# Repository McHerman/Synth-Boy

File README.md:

# Synth-Boy
## Probably the worlds smallest analog USB powered parafonic synthesizer. 

## Techical details 

The Synthboy is an analog 3 oscilator FM-enabled parafonic synthesizer, with a 4 pole voltage controlled filter, an analog ADSR envelope generator and onboard beyboard and TRS Midi control. 
The whole thing is powered from a single protected USB-C input.

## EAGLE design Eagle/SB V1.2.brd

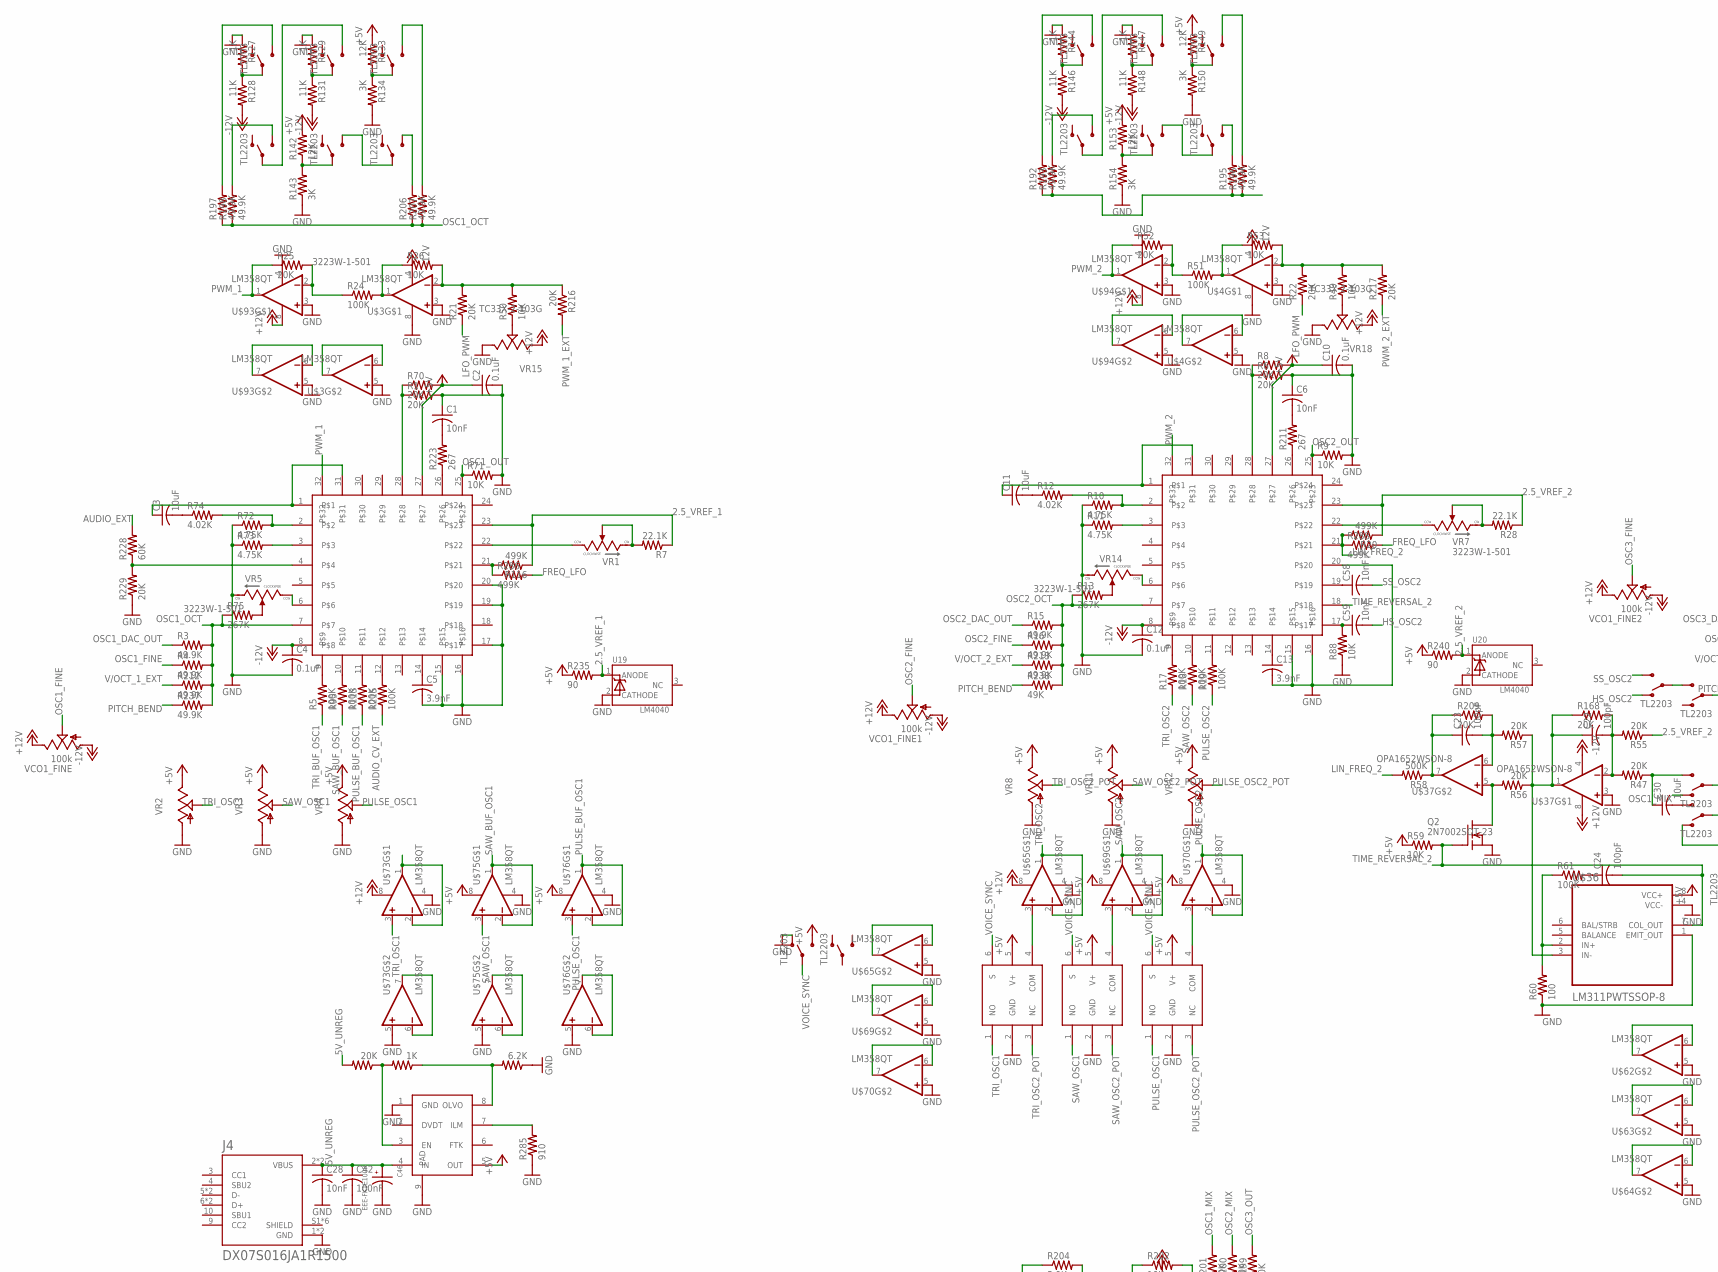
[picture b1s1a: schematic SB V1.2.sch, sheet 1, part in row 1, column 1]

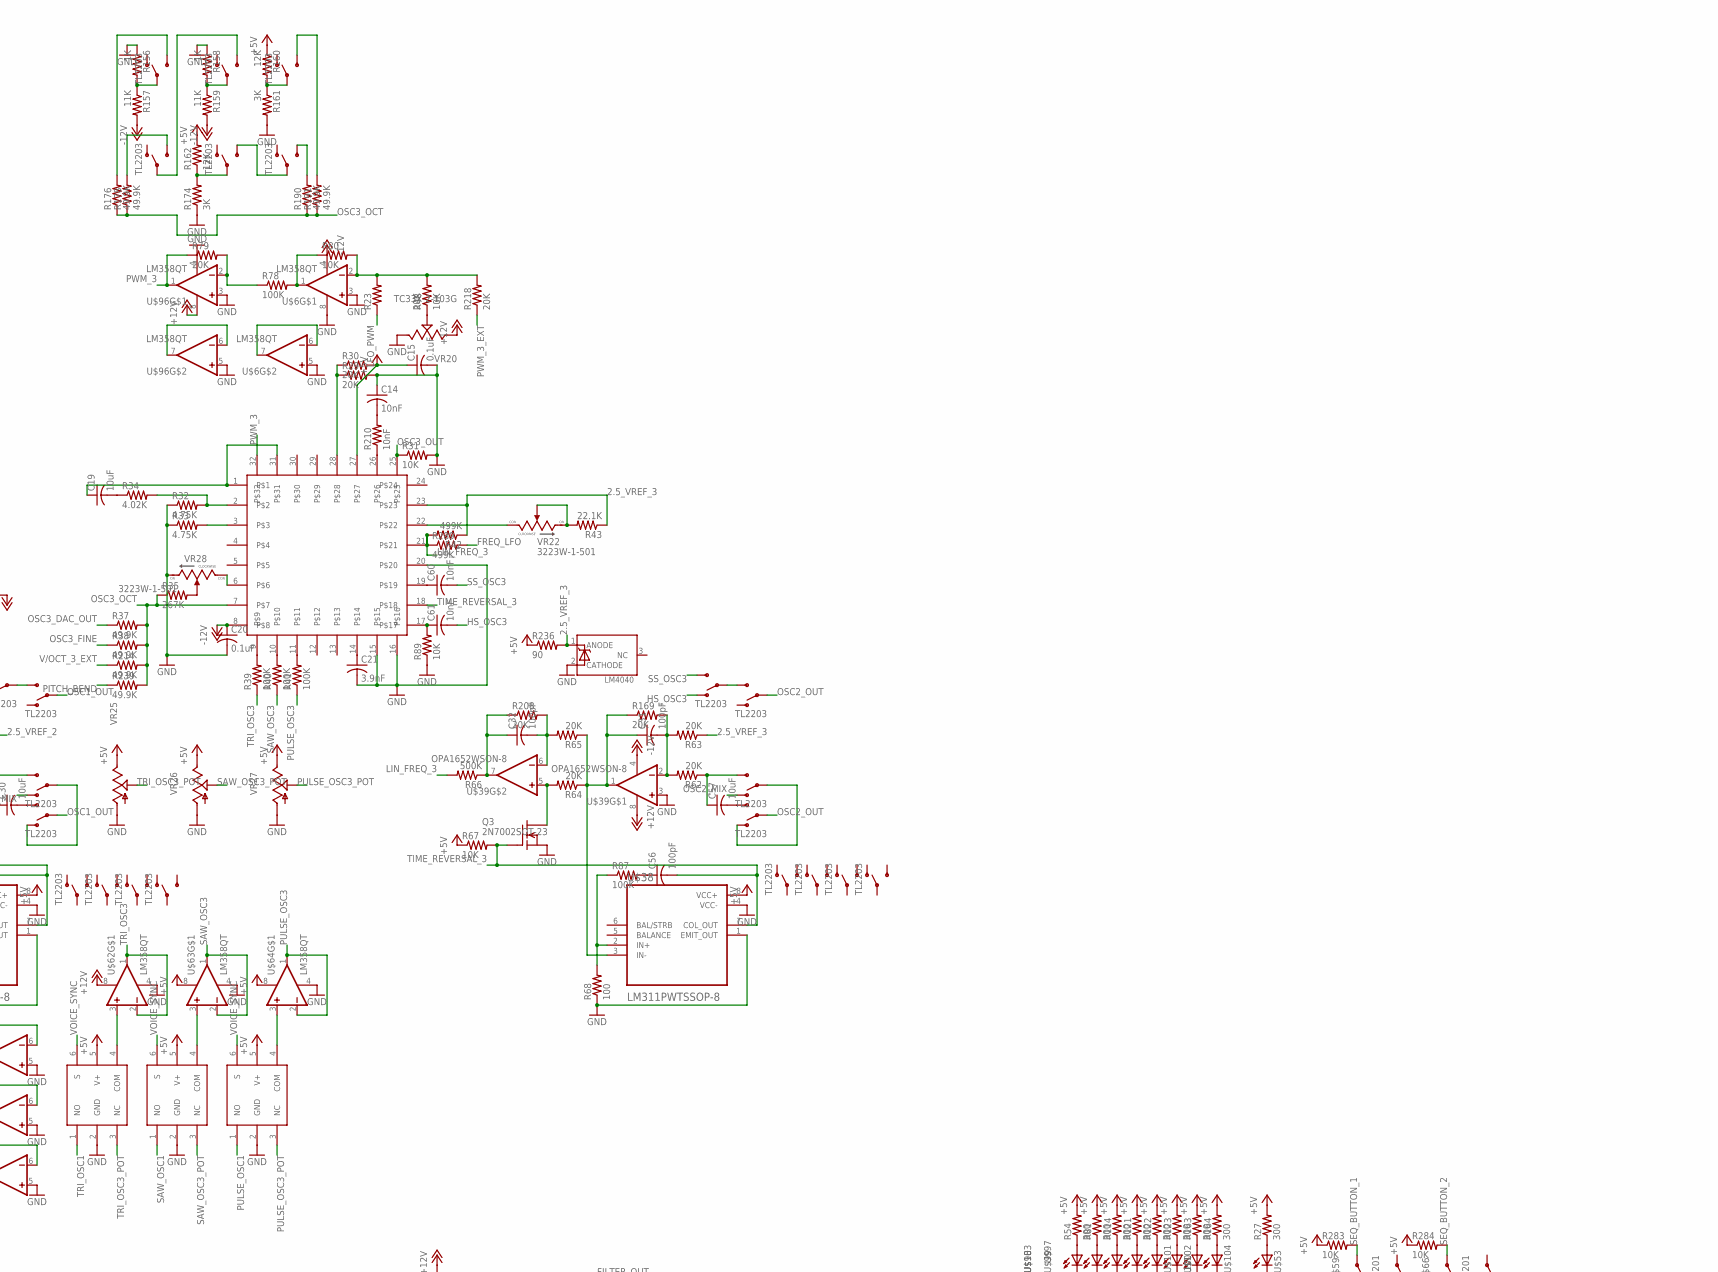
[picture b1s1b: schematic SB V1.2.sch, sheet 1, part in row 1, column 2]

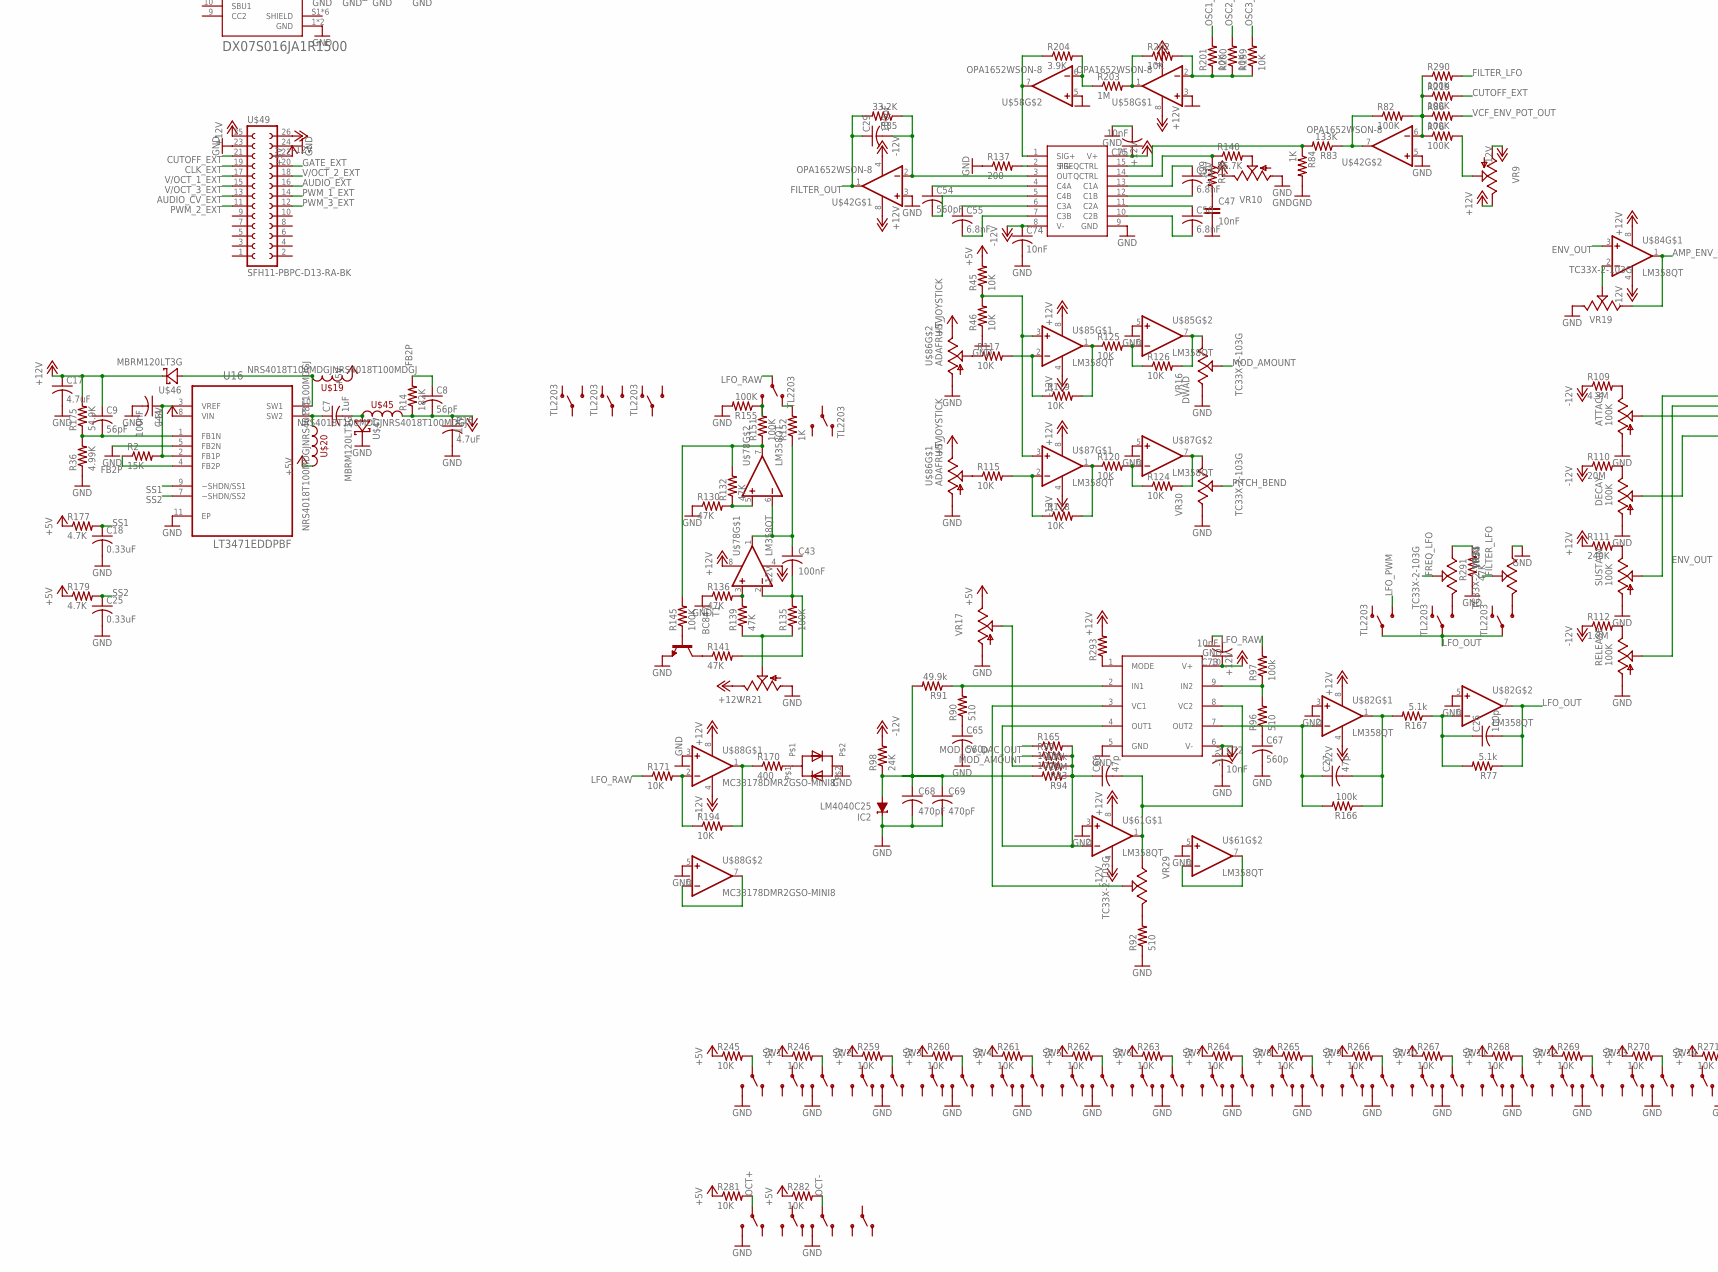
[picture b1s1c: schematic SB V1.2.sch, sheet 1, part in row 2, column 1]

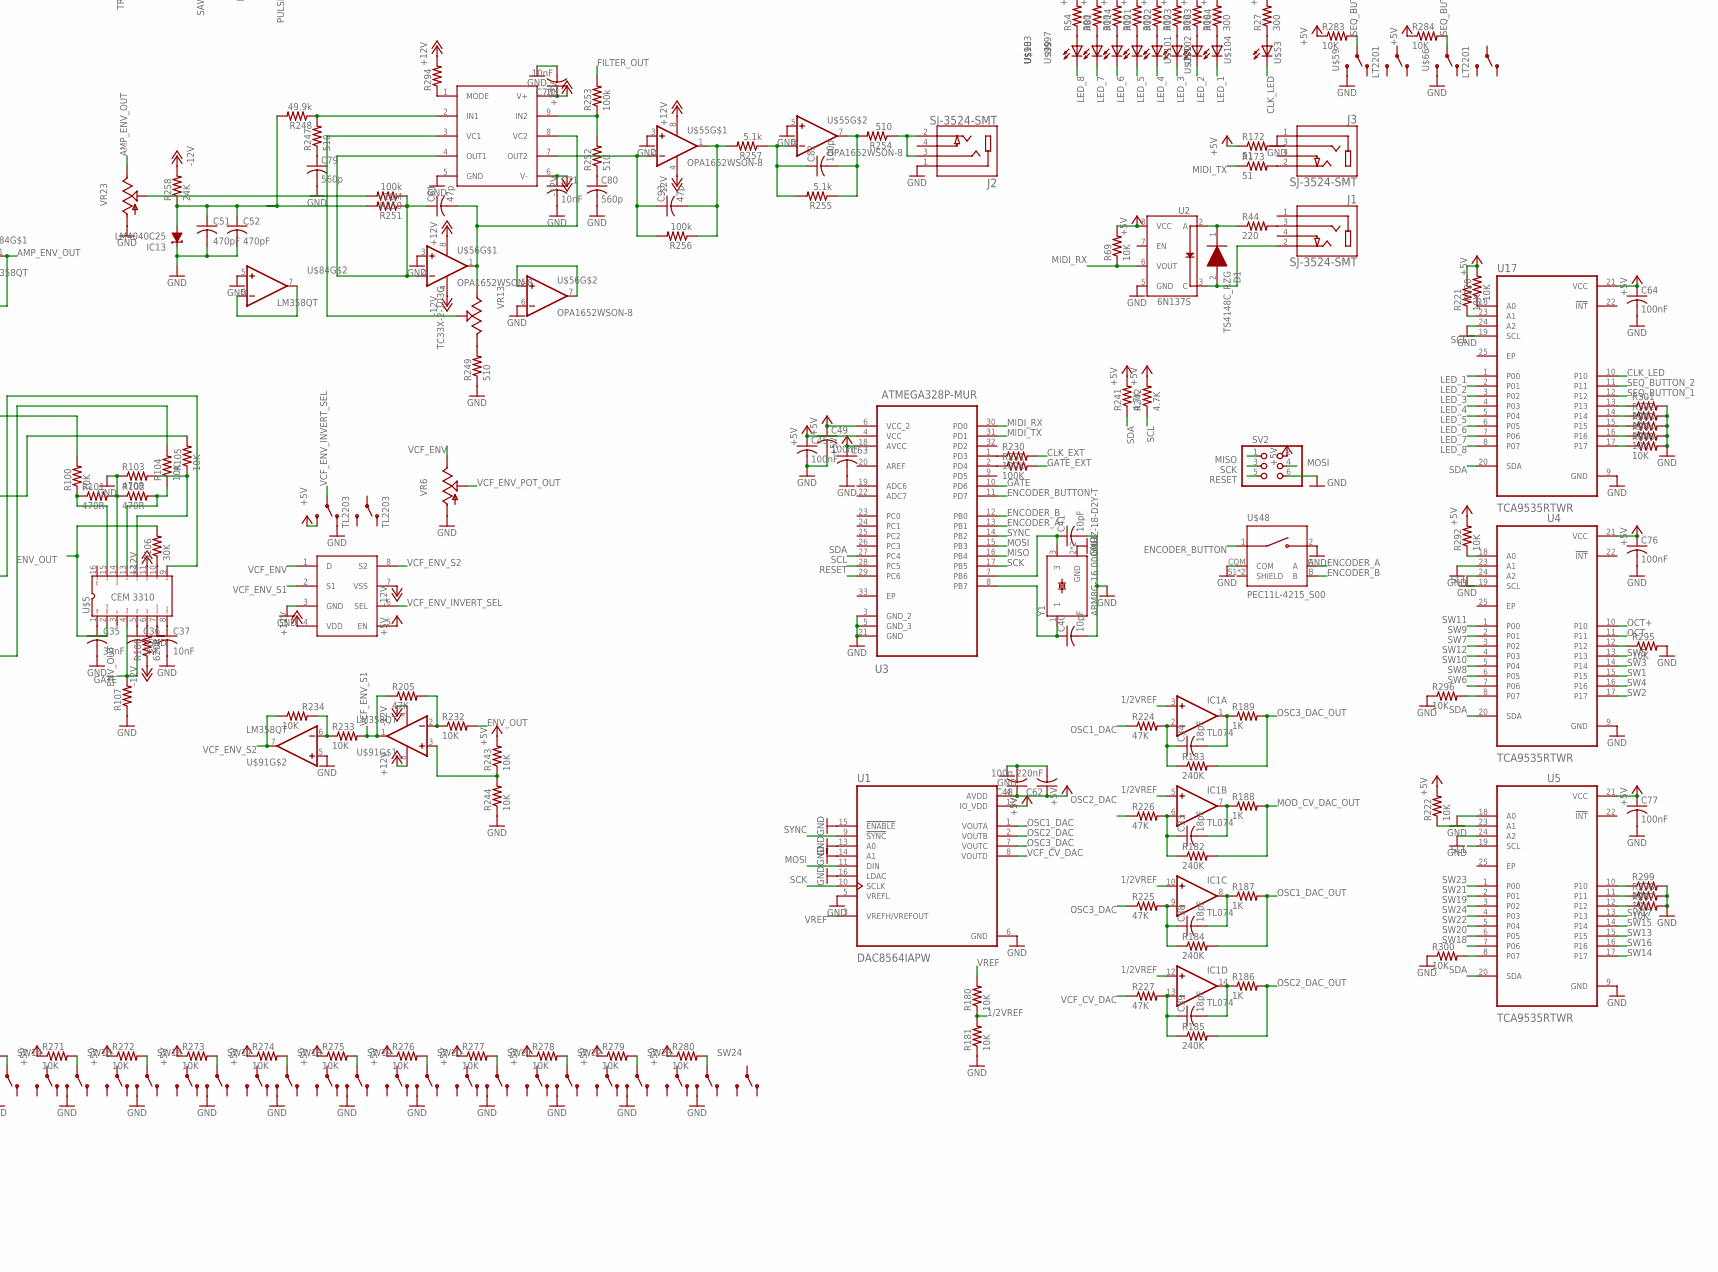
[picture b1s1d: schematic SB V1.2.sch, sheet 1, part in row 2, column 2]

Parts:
1.2K: 1K; R0402
1_DOWN, 1_UP, 2_DOWN, 2_UP, 3_DOWN, 3_UP: TL2203
4.3K: 20K; R0402
ATTACK: 100K; 9MM_SNAP-IN_POT
C1, C6, C14, C37, C47, C58, C59, C60, C61, C70, C71, C72, C73, C74, C75: 10nF; C0402
C2, C4, C10, C12, C15, C20: 0.1uF; C0402
C3, C11, C19, C30, C57: 10uF; C0603
C5, C13, C21: 3.9nF; C0603
C7: 1uF; C0805
C8, C9: 56pF; C0402
C16, C17: 4.7uF; C1206
C18, C25: 0.33uF; C0402
C22, C23, C24, C29, C31, C32, C56: 100pF; C0402
C26, C82: 100p; C0402
C27, C66, C81, C93: 47p; C0402
C28: 10nF; C0603
C33, C34, C38, C39: 18pF; C0402
C35: 39nF; C0402
C36: 3nF; C0402
C40, C41: 10pF; C0402
C42: 100nF; C0603
C43, C44, C45, C49, C64, C76, C77: 100nF; C0402
C46: EEE-FK1E100R; CAPAE430X610N
C48: 100n; C0402
C50, C53, C55: 6.8nF; C0805
C51, C52, C68, C69: 470pF; C0402
C54: 560pF; C0805
C62: 220nF; C0402
C63: C-USC0402; C0402
C65, C67, C79, C80: 560p; C0402
D1: TS4148C_RZG; DIOC1608X75N
DECAY: 100K; 9MM_SNAP-IN_POT
IC1: TL074; TSSOP14
IC2, IC13: LM4040C25; DBZ_R-PDSO-G3
J1, J2, J3: SJ-3524-SMT; CUI_SJ-3524-SMT
J4: DX07S016JA1R1500; JAE_DX07S016JA1R1500
Q2, Q3: 2N7002SOT-23; SOT23-BEC
R1, R6, R8, R21, R22, R23, R25, R29, R30, R47, R52, R55, R56, R57, R62, R63, R64, R65, R70, R79, R168, R169, R208, R209, R216, R217, R218, R229: 20K; R0402
R2: 15K; R0402
R3, R4, R15, R16, R37, R38, R176, R178, R190, R191, R192, R193, R195, R196, R197, R198, R206, R207, R212, R213, R214, R237, R239: 49.9K; R0402
R5, R17, R18, R19, R24, R39, R40, R41, R51, R61, R76, R78, R82, R86, R87, R95, R99, R113, R135, R145, R151, R155, R165, R215, R219, R230, R231, R290: 100K; R0402
R7, R28, R43: 22.1K; R0402
R9, R26, R31, R45, R46, R48, R49, R50, R53, R59, R67, R69, R71, R80, R88, R89, R100, R104, R105, R107, R115, R117, R118, R119, R120, R124, R125, R126, R171, R180, R181, R194, R199, R200, R201, R202, R220, R221, R222, R232, R233, R234, R243, R244, R245, R246, R259, R260, R261, R262, R263, R264, R265, R266, R267, R268, R269, R270, R271, R272, R273, R274, R275, R276, R277, R278, R279, R280, R281, R282, R283, R284, R292, R295, R296, R297, R298, R299, R300, R301, R302, R303, R304, R305: 10K; R0402
R10, R11, R32, R33, R72, R73: 4.75K; R0402
R12, R34, R74: 4.02K; R0402
R13, R35, R75: 267K; R0402
R14: 182K; R0402
R20, R42, R116, R286, R288, R289: 499K; R0402
R27, R54, R81, R114, R121, R122, R123, R163, R164: 300; R0603
R36: 4.99K; R0402
R44: 220; R0402
R58, R66: 500K; R0402
R60, R68: 100; R0402
R77, R167, R255, R257: 5.1k; R0402
R83: 133K; R0402
R84, R127, R129, R144, R147, R152, R156, R158, R186, R187, R188, R189: 1K; R0402
R85: 33.2K; R0402
R90, R92, R96, R247, R249, R252, R254: 510; R0402
R91, R248: 49.9k; R0402
R93, R97, R166, R250, R253, R256: 100k; R0402
R94, R110, R251: 20M; R0402
R98, R258: 24K; R0402
R101, R102, R103: 470R; R0402
R106: 30K; R0402
R108: 620R; R0402
R109: 4.3M; R0402
R111, R182, R183, R184, R185: 240K; R0402
R112: 1.8M; R0402
R128, R131, R146, R148, R157, R159: 11K; R0402
R130, R132, R136, R139, R141, R205, R224, R225, R226, R227, R291: 47K; R0402
R133, R142, R149, R153, R160, R162: 12K; R0402
R134, R143, R150, R154, R161, R174: 3K; R0402
R137: 200; R0402
R138: 499; R0402
R140: 26.7K; R0402
R170: 400; R0603
R172, R173: 51; R0402
R175: 54.9K; R0402
R177, R179, R241, R242: 4.7K; R0402
R203: 1M; R0402
R204: 3.9K; R0402
R210: 10nF; R0402
R211, R223: 267; R0402
R228: 60K; R0402
R235, R236, R240: 90; R0402
R238: 49K; R0402
R285: 910; R0402
R287: 6.2K; R0402
R293, R294: R-US_R0402; R0402
RELEASE: 100K; 9MM_SNAP-IN_POT
SUSTAIN: 100K; 9MM_SNAP-IN_POT
SV2: PINHD-2X3; 2X03
T1: BC847; SOT23
U1: DAC8564IAPW; SOP65P640X120-16N
U2: 6N137S; 8-SMD
U3: ATMEGA328P-MUR; QFN50P500X500X100-33N
U4, U5, U17: TCA9535RTWR; QFN50P400X400X80-25N
U16: LT3471EDDPBF; DFN300X300X80-11N
U19, U20, U21: LM4040; SOT23-3
U$1, U$2, U$7: SSI2130_V2QFN-32; QFN40P400X400X80-33T270N
U$3, U$4, U$6, U$61, U$62, U$63, U$64, U$65, U$69, U$70, U$73, U$75, U$76, U$78, U$82, U$84, U$85, U$87, U$91, U$93, U$94, U$96: LM358QT; SON50P200X200X60-9N
U$5: AS3310DSO-16; SO16
U$8, U$35, U$40, U$41, U$43, U$44, U$51, U$57, U$60, U$71, U$72, U$77, U$79, U$80, U$81, U$92, U$95: TL2203
U$9, U$10, U$11, U$12, U$13, U$14, U$15, U$16, U$17, U$18, U$21, U$22, U$23, U$24, U$25, U$26, U$27, U$28, U$29, U$30, U$31, U$32, U$33, U$34, U$59, U$66, U$67, U$68: LT2201
U$19, U$20, U$45: NRS4018T100MDGJNRS4018T100MDGJ; INDDFN400X400X180-2N
U$36, U$38: LM311PWTSSOP-8; TSSOP8
U$37, U$39, U$42, U$55, U$56, U$58: OPA1652WSON-8; SON50P300X300X80-9T120X200N
U$46, U$47: MBRM120LT3G; DIO_MBRM110LT1G
U$48: PEC11L-4215_S00; XDCR_PEC11R-4215F-S0024
U$49: SFH11-PBPC-D13-RA-BK; FE13-2W
U$53, U$97, U$98, U$99, U$100, U$101, U$102, U$103, U$104: WP914HDT
U$54, U$90: SSI2162SSOP10; SOP100P600X150-10N
U$74: WP483SRSGW
U$83: SSI2144; TSSOP16
U$86: ADAFRUIT_JOYSTICK; ADAFRUIT-JOYSTICK
U$88: MC33178DMR2GSO-MINI8; SOP65P490X110-8N
U$89: TMUX6219DGKRSO-MINI8; SOP65P490X110-8N
U$105, U$106, U$107, U$108, U$109, U$110: NC7SB3157P6XSC-70-6; SOT65P210X110-6N
U$111: TPS259620DDARSOIC-8; SOIC127P600X170-9T240X310N
VCO1_FINE, VCO1_FINE1, VCO1_FINE2: 100k; 9MM_SNAP-IN_POT
VR1, VR5, VR7, VR14, VR22, VR28: 3223W-1-501; TRIM_3223W-1-501
VR2, VR3, VR4, VR6, VR8, VR9, VR10, VR11, VR12, VR17, VR23, VR25, VR26, VR27: 9MM_SNAP-IN_POT_; 9MM_SNAP-IN_POT
VR13, VR15, VR16, VR18, VR19, VR20, VR24, VR29, VR30, VR31: TC33X-2-103G; TRIMMER_TC33X-2-103G
VR21: 9MM_SNAP-IN_POT_NOSNAP_; 9MM_SNAP-IN_POT
Y1: ABM8G-16.000MHZ-18-D2Y-T; OSCSC320X250X100N

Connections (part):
1/2VREF: IC1.3 (+IN), IC1.5 (+IN), IC1.10 (+IN), IC1.12 (+IN), R180.1, R181.2
2.5_VREF_1: R7.1, R116.1, R235.2, U19.1 (ANODE), U$7.23
2.5_VREF_2: R20.1, R28.1, R55.1, R240.2, U20.1 (ANODE), U$1.23
2.5_VREF_3: R42.1, R43.1, R63.1, R236.2, U21.1 (ANODE), U$2.23
5V_UNREG: 4.3K.2, C28.1, C42.1, C46.1, J4.2 (VBUS), J4.11 (VBUS), U$111.4 (IN)
+5V: C2.1, C10.1, C15.1, C45.1, C48.1, C49.1, C62.1, C63.1, C64.1, C76.1, C77.1, R8.2, R27.2, R30.2, R45.2, R54.2, R59.1, R67.1, R69.2, R70.2, R81.2, R114.2, R121.2, R122.2, R123.2, R133.1, R142.2, R149.1, R153.2, R160.1, R162.2, R163.2, R164.2, R172.1, R177.1, R179.1, R220.2, R221.2, R222.2, R235.1, R236.1, R240.1, R241.2, R242.2, R243.2, R245.1, R246.1, R259.1, R260.1, R261.1, R262.1, R263.1, R264.1, R265.1, R266.1, R267.1, R268.1, R269.1, R270.1, R271.1, R272.1, R273.1, R274.1, R275.1, R276.1, R277.1, R278.1, R279.1, R280.1, R281.1, R282.1, R283.1, R284.1, R292.2, SV2.2, U1.4 (AVDD), U1.12 (IO_VDD), U2.8 (VCC), U3.4 (VCC), U3.6 (VCC_2)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
+12V: C9.1, C17.1, C70.1, C73.1, C75.1, IC1.4 (V+), R111.1, R175.2, R293.2, R294.2, U$5.11, U$37.8 (V+), U$39.8 (V+), U$42.8 (V+), U$46.1 (K), U$49.25, U$54.10 (V+), U$55.8 (V+), U$56.8 (V+), U$58.8 (V+), U$61.8 (V+), U$62.8 (V+), U$65.8 (V+), U$73.8 (V+), U$78.8 (V+), U$82.8 (V+), U$83.16 (V+), U$84.8 (V+), U$85.8 (V+), U$87.8 (V+), U$88.8 (V+), U$89.4 (VDD), U$90.10 (V+), U$91.8 (V+), U$93.8 (V+), U$94.8 (V+), U$96.8 (V+), VCO1_FINE.3 (E), VCO1_FINE1.3 (E), VCO1_FINE2.3 (E), VR9.3 (E), VR10.3 (E), VR15.1 (CCW), VR18.1 (CCW), VR20.1 (CCW), VR21.3 (E)
-12V: C4.1, C8.2, C12.1, C16.1, C20.1, C71.1, C72.1, C74.1, IC1.11 (V-), R14.1, R98.2, R108.1, R109.1, R110.1, R112.1, R128.2, R131.2, R146.2, R148.2, R157.2, R159.2, R258.2, U$1.8, U$2.8, U$3.4 (V-), U$4.4 (V-), U$6.4 (V-), U$7.8, U$37.4 (V-), U$39.4 (V-), U$42.4 (V-), U$45.2, U$49.26, U$54.6 (V-), U$55.4 (V-), U$56.4 (V-), U$58.4 (V-), U$61.4 (V-), U$78.4 (V-), U$82.4 (V-), U$83.8 (V-), U$84.4 (V-), U$85.4 (V-), U$87.4 (V-), U$88.4 (V-), U$89.7 (VSS), U$90.6 (V-), U$91.4 (V-), VCO1_FINE.1 (A), VCO1_FINE1.1 (A), VCO1_FINE2.1 (A), VR9.1 (A)
AMP_ENV_OUT: U$84.1 (OUT), VR19.1 (CCW), VR23.3 (E)
AREF_-2.1: C51.1, C52.1, IC13.2 (A), R248.2, R251.2, R258.1
AREF_-2.2: C68.1, C69.1, IC2.2 (A), R91.2, R94.2, R98.1
AUDIO_CV_EXT: R215.1, U$49.13
AUDIO_EXT: R228.2, U$49.16
A_IN_O2B1: R247.2, R248.1, U$54.2 (IN1)
A_IN_O2B2: R90.2, R91.1, U$90.2 (IN1)
CLK_EXT: R230.2, U$49.19
CLK_LED: U17.10, U$53.C
CUTOFF_EXT: R219.2, U$49.21
DWAD: R126.2, U$85.7 (OUT), VR16.3 (CW)
ENCODER_A: U3.13 (PB1), U$48.A
ENCODER_B: U3.12 (PB0), U$48.B
ENCODER_BUTTON: U3.11 (PD7), U$48.1
ENV_OUT: R106.2, R232.2, U$5.2, U$84.3 (+IN)
FB2P: C8.1, R2.1, R14.2, U16.4 (FB2P)
FILTER_LFO: R290.2, VR31.2 (WIPER)
FILTER_OUT: C29.1, R85.2, R253.2, U$42.1 (OUT)
FREQ_LFO: R286.2, R288.2, R289.2, VR24.2 (WIPER)
GATE: C36.2, R107.2, U3.10 (PD6), U$5.4
GATE_EXT: R231.2, U$49.20
GND: ATTACK.1 (A), C1.1, C2.2, C4.2, C5.2, C6.1, C10.2, C12.2, C13.2, C14.1, C15.2, C16.2, C17.2, C18.2, C20.2, C21.2, C25.2, C28.2, C35.2, C37.2, C40.2, C41.2, C42.2, C44.2, C45.2, C46.2, C47.2, C48.2, C49.2, C51.2, C52.2, C62.2, C63.2, C64.2, C65.2, C67.2, C68.2, C69.2, C70.2, C71.2, C72.2, C73.2, C74.2, C75.2, C76.2, C77.2, C79.2, C80.2, DECAY.1 (A), IC2.1 (C), IC13.1 (C), J2.1, J3.1, J4.1 (GND), J4.12 (GND), Q2.C (S), Q3.C (S), R1.2, R6.2, R9.2, R10.1, R11.1, R29.2, R31.2, R32.1, R33.1, R36.1, R46.1, R60.1, R68.1, R71.2, R72.1, R73.1, R84.2, R88.1, R89.1, R92.1, R101.2, R102.1, R103.1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
HS_OSC2: C59.2, U$51.P$3 (O1)
HS_OSC3: C61.2, U$57.P$3 (O1)
LED_1: U17.1 (P00), U$104.C
LED_2: U17.2 (P01), U$103.C
LED_3: U17.3 (P02), U$102.C
LED_4: U17.4 (P03), U$101.C
LED_5: U17.5 (P04), U$100.C
LED_6: U17.6 (P05), U$99.C
LED_7: U17.7 (P06), U$98.C
LED_8: U17.8 (P07), U$97.C
LFO_OUT: C26.2, R77.1, U$79.P$2 (COMMON1), U$80.P$2 (COMMON1), U$81.P$2 (COMMON1), U$82.7 (OUT)
LFO_PWM: R21.1, R22.1, R23.1, U$79.P$1 (S1)
LFO_RAW: R97.2, R171.1, U$77.P$2 (COMMON1)
LIN_FREQ_2: R20.2, R58.2, R288.1, U$1.21
LIN_FREQ_3: R42.2, R66.2, R289.1, U$2.21
MIDI_RX: R69.1, U2.6 (VOUT), U3.30 (PD0)
MIDI_TX: R173.1, U3.31 (PD1)
MISO: SV2.1, U3.16 (PB4)
MIX2_OUT: R204.1, U$58.7 (OUT), U$83.1 (SIG+)
MOD_AMOUNT: R99.1, VR16.2 (WIPER)
MOD_CV_DAC_OUT: R165.1, R182.2, R188.2
MOSI: SV2.4, U1.11 (DIN), U3.15 (PB3)
unnamed: R5.2, U$7.9
unnamed: C30.2, U$8.P$1 (S1)
unnamed: C57.2, U$40.P$1 (S1)
unnamed: R116.2, R286.1, U$7.21
unnamed: U$7.22, VR1.1
unnamed: R7.2, VR1.2, VR1.3
unnamed: U$84.2 (-IN), VR19.2 (WIPER)
unnamed: R6.1, R8.1, U$1.28
unnamed: U$8.P$3 (O1), U$35.P$2 (COMMON1)
unnamed: U$7.6, VR5.1
unnamed: R210.1, U$2.26
unnamed: R27.1, U$53.A
unnamed: R75.2, VR5.2
unnamed: U$40.P$3 (O1), U$41.P$2 (COMMON1)
unnamed: R10.2, R12.2, U$1.2
unnamed: C11.2, R12.1
unnamed: C11.1, U$1.1, U$1.31
unnamed: R132.2, R145.2, R151.1, U$78.7 (OUT)
unnamed: R17.2, U$1.9
unnamed: R18.2, U$1.10
unnamed: R19.2, U$1.11
unnamed: C13.1, U$1.14
unnamed: R54.1, U$97.A
unnamed: U$93.6 (-IN), U$93.7 (OUT)
unnamed: U$1.22, VR7.1
unnamed: R29.1, R30.1, U$2.28
unnamed: R24.2, R26.1, U$3.1 (OUT)
unnamed: R28.2, VR7.2, VR7.3
unnamed: U$65.3 (+IN), U$105.4 (COM)
unnamed: R24.1, R25.2, U$93.2 (-IN)
unnamed: R199.1, R200.1, R201.1, R202.2, U$58.2 (-IN)
unnamed: R170.2, U$74.P$1
unnamed: R11.2, U$1.3
unnamed: U$43.P$1 (S1), U$51.P$2 (COMMON1)
unnamed: C44.1, R2.2, U16.2 (FB1P), U16.3 (VREF)
unnamed: U$1.6, VR14.1
unnamed: R13.2, VR14.2
unnamed: U$44.P$1 (S1), U$57.P$2 (COMMON1)
unnamed: U$69.3 (+IN), U$106.4 (COM)
unnamed: C22.2, R47.2, R55.2, R168.2, U$37.2 (-IN)
unnamed: C14.2, R210.2
unnamed: R32.2, R34.2, U$2.2
unnamed: C19.2, R34.1
unnamed: C19.1, U$2.1, U$2.31
unnamed: C9.2, R36.2, R175.1, U16.1 (FB1N)
unnamed: R39.2, U$2.9
unnamed: R40.2, U$2.10
unnamed: R41.2, U$2.11
unnamed: C21.1, U$2.14
unnamed: U$70.3 (+IN), U$107.4 (COM)
unnamed: U$2.22, VR22.1
unnamed: R43.2, VR22.2, VR22.3
unnamed: R33.2, U$2.3
unnamed: C22.1, R56.1, R57.1, R168.1, U$36.3 (IN-), U$37.1 (OUT)
unnamed: U$2.6, VR28.1
unnamed: R35.2, VR28.2
unnamed: C32.2, R65.2, R208.2, U$39.6 (-IN)
unnamed: C23.1, R58.1, R209.1, U$37.7 (OUT)
unnamed: Q3.E (D), R64.2, U$39.5 (+IN)
unnamed: R51.2, R53.1, U$4.1 (OUT)
unnamed: R51.1, R52.2, U$94.2 (-IN)
unnamed: C43.1, R152.1, U$78.1 (OUT), U$78.6 (-IN)
unnamed: R171.2, R194.1, U$88.2 (-IN)
unnamed: R60.2, R61.1, U$36.2 (IN+)
unnamed: C24.1, R61.2
unnamed: U$62.3 (+IN), U$108.4 (COM)
unnamed: C30.1, R47.1, U$35.P$1 (S1)
unnamed: R115.1, U$86.P$2 (S)
unnamed: C31.2, R62.2, R63.2, R169.2, U$39.2 (-IN)
unnamed: C31.1, R64.1, R65.1, R169.1, U$38.3 (IN-), U$39.1 (OUT)
unnamed: Q2.E (D), R56.2, U$37.5 (+IN)
unnamed: C32.1, R66.1, R208.1, U$39.7 (OUT)
unnamed: C23.2, R57.2, R209.2, U$37.6 (-IN)
unnamed: R68.2, R87.1, U$38.2 (IN+)
unnamed: C56.1, R87.2
unnamed: C57.1, R62.1, U$41.P$1 (S1)
unnamed: R1.1, R70.1, U$7.28
unnamed: R211.1, U$1.26
unnamed: R72.2, R74.2, U$7.2
unnamed: C3.2, R74.1
unnamed: C3.1, U$7.1, U$7.31
unnamed: C7.1, U16.6 (SW2), U$20.1
unnamed: R78.2, R80.1, U$6.1 (OUT)
unnamed: R78.1, R79.2, U$96.2 (-IN)
unnamed: R136.2, R139.2, U$78.3 (+IN)
unnamed: D1.1 (K), R44.1, U2.2 (A)
unnamed: D1.2 (A), J1.2, U2.3 (C)
unnamed: R170.1, R194.2, U$88.1 (OUT)
unnamed: J1.3, R44.2
unnamed: U$88.6 (-IN), U$88.7 (OUT)
unnamed: C6.2, R211.2
unnamed: R95.2, U$7.10
unnamed: R113.2, U$7.11
unnamed: C58.1, U$1.19
unnamed: R233.1, R234.2, U$91.6 (-IN)
unnamed: C59.1, R88.2, U$1.17
unnamed: R76.1, R82.2, R86.1, R219.1, R290.1, U$42.6 (-IN)
unnamed: R221.1, U17.23 (A1)
unnamed: C66.1, R93.1, R94.1, R99.2, R165.2, U$61.2 (-IN), U$90.4 (OUT1)
unnamed: C61.1, R89.2, U$2.17
unnamed: C93.1, R256.2, U$54.7 (OUT2), U$55.2 (-IN)
unnamed: R76.2, VR9.2 (S)
unnamed: C60.1, U$2.19
unnamed: U$63.3 (+IN), U$109.4 (COM)
unnamed: U$64.3 (+IN), U$110.4 (COM)
unnamed: U$62.6 (-IN), U$62.7 (OUT)
unnamed: U$63.6 (-IN), U$63.7 (OUT)
unnamed: U$64.6 (-IN), U$64.7 (OUT)
unnamed: U$65.6 (-IN), U$65.7 (OUT)
unnamed: U$69.6 (-IN), U$69.7 (OUT)
unnamed: U$70.6 (-IN), U$70.7 (OUT)
unnamed: R117.1, U$86.P$5 (S)
unnamed: C5.1, U$7.14
unnamed: R81.1, U$98.A
unnamed: R117.2, R119.1, U$85.2 (-IN)
unnamed: U$73.6 (-IN), U$73.7 (OUT)
unnamed: U$75.6 (-IN), U$75.7 (OUT)
unnamed: U$76.6 (-IN), U$76.7 (OUT)
unnamed: C65.1, R90.1
unnamed: R92.2, VR29.3 (CW)
unnamed: U$90.3 (VC1), VR29.2 (WIPER)
unnamed: C66.2, U$61.1 (OUT), U$90.8 (VC2), VR29.1 (CCW)
unnamed: C67.1, R96.1
unnamed: C27.1, R166.2, U$82.2 (-IN), U$90.7 (OUT2)
unnamed: C55.1, U$83.6 (C3A)
unnamed: R96.2, R97.1, U$90.9 (IN2)
unnamed: R119.2, R125.1, U$85.1 (OUT)
unnamed: R100.1, R101.1, U$5.15
unnamed: R106.1, U$5.10
unnamed: R102.2, R104.1, U$5.13
unnamed: R103.2, R105.1, U$5.12
unnamed: R82.1, R83.1, U$42.7 (OUT)
unnamed: J3.3, R172.2
unnamed: C35.1, U$5.1
unnamed: C36.1, U$5.5
unnamed: C37.1, U$5.8
unnamed: C7.2, U$45.1, U$47.2 (A)
unnamed: J3.2, R173.2
unnamed: R108.2, U$5.6
unnamed: ATTACK.3 (E), R109.2
unnamed: DECAY.3 (E), R110.2
unnamed: R111.2, SUSTAIN.3 (E)
unnamed: R112.2, RELEASE.3 (E)
unnamed: ATTACK.2 (S), R100.2
unnamed: DECAY.2 (S), R105.2
unnamed: SUSTAIN.2 (S), U$5.9
unnamed: R104.2, RELEASE.2 (S)
unnamed: R205.2, R232.1, U$91.2 (-IN)
unnamed: R115.2, R118.1, U$87.2 (-IN)
unnamed: U$84.6 (-IN), U$84.7 (OUT)
unnamed: R223.1, U$7.26
unnamed: U$80.P$1 (S1), VR24.3 (CW)
unnamed: C1.2, R223.2
unnamed: C34.1, IC1.2 (-IN), R183.1, R224.2
unnamed: R73.2, U$7.3
unnamed: R93.2, VR17.2 (S)
unnamed: R118.2, R120.1, U$87.1 (OUT)
unnamed: R120.2, R124.1, U$87.6 (-IN)
unnamed: R114.1, U$99.A
unnamed: R124.2, U$87.7 (OUT), VR30.3 (CW)
unnamed: R125.2, R126.1, U$85.6 (-IN)
unnamed: C39.1, IC1.13 (-IN), R185.1, R227.2
unnamed: C43.2, R135.2, R141.2, U$78.2 (-IN)
unnamed: R250.2, VR23.2 (S)
unnamed: 1_DOWN.P$2 (COMMON1), R127.2, R128.1
unnamed: C38.1, IC1.9 (-IN), R184.1, R225.2
unnamed: C41.1, U3.7 (PB6), Y1.3
unnamed: C33.1, IC1.6 (-IN), R182.1, R226.2
unnamed: C40.1, U3.8 (PB7), Y1.1
unnamed: R129.2, R131.1, U$92.P$2 (COMMON1)
unnamed: U16.10 (SW1), U$19.2, U$46.2 (A)
unnamed: C79.1, R247.1
unnamed: 1_UP.P$5 (COMMON1), R133.2, R134.1
unnamed: R142.1, R143.2, U$92.P$5 (COMMON1)
unnamed: R135.1, R139.1, VR21.2 (S)
unnamed: 1_UP.P$2 (COMMON1), U$92.P$4 (S1)
unnamed: 1_DOWN.P$5 (COMMON1), U$92.P$1 (S1)
unnamed: R202.1, R203.2, U$58.1 (OUT)
unnamed: R141.1, T1.3 (C)
unnamed: C55.2, U$83.7 (C3B)
unnamed: R145.1, T1.1 (B)
unnamed: C53.1, U$83.13 (C1A)
unnamed: 1_DOWN.P$1 (S1), R197.2
unnamed: 1_DOWN.P$4 (S1), R198.2
unnamed: R121.1, U$100.A
unnamed: R122.1, U$101.A
unnamed: R130.2, R132.1, U$78.5 (+IN)
unnamed: C53.2, U$83.12 (C1B)
unnamed: R151.2, R155.1, U$77.P$1 (S1)
unnamed: C50.1, U$83.11 (C2A)
unnamed: R152.2, U$77.P$3 (O1)
unnamed: C50.2, U$83.10 (C2B)
unnamed: 1_UP.P$1 (S1), R206.2
unnamed: 1_UP.P$4 (S1), R207.2
unnamed: 2_DOWN.P$2 (COMMON1), R144.2, R146.1
unnamed: R147.2, R148.1, U$60.P$2 (COMMON1)
unnamed: R123.1, U$102.A
unnamed: 2_UP.P$5 (COMMON1), R149.2, R150.1
unnamed: R163.1, U$103.A
unnamed: R153.1, R154.2, U$60.P$5 (COMMON1)
unnamed: R164.1, U$104.A
unnamed: 2_UP.P$2 (COMMON1), U$60.P$4 (S1)
unnamed: R45.1, R46.2, U$85.3 (+IN), U$87.3 (+IN)
unnamed: C34.2, IC1.1 (OUT), R189.1
unnamed: C33.2, IC1.7 (OUT), R188.1
unnamed: C38.2, IC1.8 (OUT), R187.1
unnamed: C39.2, IC1.14 (OUT), R186.1
unnamed: R297.1, U5.12
unnamed: R298.1, U5.11
unnamed: R299.1, U5.10
unnamed: R300.2, U5.8 (P07)
unnamed: R243.1, R244.2, U$91.3 (+IN)
unnamed: R295.1, U4.12
unnamed: R228.1, R229.2, U$7.4
unnamed: U$81.P$1 (S1), VR31.3 (CW)
unnamed: R296.2, U4.8 (P07)
unnamed: R230.1, U3.1 (PD3)
unnamed: R231.1, U3.2 (PD4)
unnamed: U$3.6 (-IN), U$3.7 (OUT)
unnamed: U$94.6 (-IN), U$94.7 (OUT)
unnamed: C26.1, R77.2, R167.1, U$82.6 (-IN)
unnamed: C27.2, R166.1, R167.2, U$82.1 (OUT)
unnamed: U$61.6 (-IN), U$61.7 (OUT)
unnamed: U$4.6 (-IN), U$4.7 (OUT)
unnamed: U$6.6 (-IN), U$6.7 (OUT)
unnamed: U$96.6 (-IN), U$96.7 (OUT)
unnamed: R291.2, VR24.1 (CCW)
unnamed: R220.1, U17.18 (A0)
unnamed: R222.1, U5.23 (A1)
unnamed: R292.1, U4.18 (A0)
unnamed: R83.2, R84.1, U$83.15 (FREQCTRL)
unnamed: C54.1, U$83.4 (C4A)
unnamed: C54.2, U$83.5 (C4B)
unnamed: R137.2, U$83.2 (SIG-)
unnamed: R138.1, R140.1, U$83.14 (QCTRL)
unnamed: C47.1, R138.2
unnamed: C29.2, R85.1, U$42.2 (-IN), U$83.3 (OUT)
unnamed: 2_DOWN.P$5 (COMMON1), U$60.P$1 (S1)
unnamed: 2_DOWN.P$1 (S1), R192.2
unnamed: 2_DOWN.P$4 (S1), R193.2
unnamed: 2_UP.P$1 (S1), R195.2
unnamed: 2_UP.P$4 (S1), R196.2
unnamed: 3_DOWN.P$2 (COMMON1), R156.2, R157.1
unnamed: R158.2, R159.1, U$95.P$2 (COMMON1)
unnamed: 3_UP.P$5 (COMMON1), R160.2, R161.1
unnamed: R162.1, R174.2, U$95.P$5 (COMMON1)
unnamed: 3_UP.P$2 (COMMON1), U$95.P$4 (S1)
unnamed: 3_DOWN.P$5 (COMMON1), U$95.P$1 (S1)
unnamed: 3_DOWN.P$1 (S1), R176.2
unnamed: 3_DOWN.P$4 (S1), R178.2
unnamed: 3_UP.P$1 (S1), R190.2
unnamed: 3_UP.P$4 (S1), R191.2
unnamed: R293.1, U$90.1 (MODE)
unnamed: 1.2K.2, 4.3K.1, U$111.3 (EN)
unnamed: R215.2, U$7.12
unnamed: R294.1, U$54.1 (MODE)
unnamed: R301.1, U17.13
unnamed: R302.1, U17.14
unnamed: R140.2, VR10.2 (S)
unnamed: R285.2, U$111.7 (ILM)
unnamed: R21.2, R26.2, R50.2, R216.1, U$3.2 (-IN)
unnamed: R22.2, R49.2, R53.2, R217.2, U$4.2 (-IN)
unnamed: R23.2, R48.2, R80.2, R218.2, U$6.2 (-IN)
unnamed: R50.1, VR15.2 (WIPER)
unnamed: R49.1, VR18.2 (WIPER)
unnamed: R48.1, VR20.2 (WIPER)
unnamed: 1.2K.1, R287.2, U$111.8 (OLVO)
unnamed: R303.1, U17.15
unnamed: R203.1, R204.2, U$58.6 (-IN)
unnamed: R304.1, U17.16
unnamed: R249.2, VR13.3 (CW)
unnamed: U$54.3 (VC1), VR13.2 (WIPER)
unnamed: C81.2, U$54.8 (VC2), U$56.1 (OUT), VR13.1 (CCW)
unnamed: R305.1, U17.17
unnamed: C80.1, R252.1
unnamed: C82.1, R255.2, R257.1, U$55.6 (-IN)
unnamed: C93.2, R256.1, R257.2, U$55.1 (OUT)
unnamed: R252.2, R253.1, U$54.9 (IN2)
unnamed: U$56.5 (+IN), U$56.7 (OUT)
unnamed: C81.1, R250.1, R251.1, U$54.4 (OUT1), U$56.2 (-IN)
unnamed: J2.2, J2.3, R254.1
OCT+: R281.2, U4.10, U$67.2
OCT-: R282.2, U4.11, U$68.2
OSC1_DAC: R224.1, U1.1 (VOUTA)
OSC1_DAC_OUT: R3.1, R184.2, R187.2
OSC1_FINE: R4.1, VCO1_FINE.2 (S)
OSC1_MIX: R201.2, U$35.P$3 (O1)
OSC1_OCT: R3.2, R4.2, R75.1, R197.1, R198.1, R206.1, R207.1, R212.2, R237.2, U$7.7
OSC1_OUT: R71.1, U$7.25, U$8.P$2 (COMMON1), U$43.P$2 (COMMON1)
OSC2_DAC: R226.1, U1.2 (VOUTB)
OSC2_DAC_OUT: R15.1, R185.2, R186.2
OSC2_FINE: R16.1, VCO1_FINE1.2 (S)
OSC2_MIX: R200.2, U$41.P$3 (O1)
OSC2_OCT: R13.1, R15.2, R16.2, R192.1, R193.1, R195.1, R196.1, R213.2, R238.2, U$1.7
OSC2_OUT: R9.1, U$1.25, U$40.P$2 (COMMON1), U$44.P$2 (COMMON1)
OSC3_DAC: R225.1, U1.7 (VOUTC)
OSC3_DAC_OUT: R37.1, R183.2, R189.2
OSC3_FINE: R38.1, VCO1_FINE2.2 (S)
OSC3_OCT: R35.1, R37.2, R38.2, R176.1, R178.1, R190.1, R191.1, R214.2, R239.2, U$2.7
OSC3_OUT: R31.1, R199.2, U$2.25
OUT5: C82.2, R254.2, R255.1, U$55.7 (OUT)
PITCH_BEND: R237.1, R238.1, R239.1, VR30.2 (WIPER)
PULSE_BUF_OSC1: R113.1, U$76.1 (OUT), U$76.2 (-IN)
PULSE_OSC1: U$76.3 (+IN), U$107.1 (NO), U$110.1 (NO), VR4.2 (S)
PULSE_OSC2: R19.1, U$70.1 (OUT), U$70.2 (-IN)
PULSE_OSC2_POT: U$107.3 (NC), VR12.2 (S)
PULSE_OSC3: R41.1, U$64.1 (OUT), U$64.2 (-IN)
PULSE_OSC3_POT: U$110.3 (NC), VR27.2 (S)
PWM_1: R25.1, U$7.32, U$93.1 (OUT)
PWM_1_EXT: R216.2, U$49.14
PWM_2: R52.1, U$1.32, U$94.1 (OUT)
PWM_2_EXT: R217.1, U$49.11
PWM_3: R79.1, U$2.32, U$96.1 (OUT)
PWM_3_EXT: R218.1, U$49.12
RESET: SV2.5, U3.29 (PC6)
SAW_BUF_OSC1: R95.1, U$75.1 (OUT), U$75.2 (-IN)
SAW_OSC1: U$75.3 (+IN), U$106.1 (NO), U$109.1 (NO), VR3.2 (S)
SAW_OSC2: R18.1, U$69.1 (OUT), U$69.2 (-IN)
SAW_OSC2_POT: U$106.3 (NC), VR11.2 (S)
SAW_OSC3: R40.1, U$63.1 (OUT), U$63.2 (-IN)
SAW_OSC3_POT: U$109.3 (NC), VR26.2 (S)
SCK: SV2.3, U1.10 (SCLK), U3.17 (PB5)
SCL: R242.1, U3.28 (PC5), U4.19 (SCL), U5.19 (SCL), U17.19 (SCL)
SDA: R241.1, U3.27 (PC4), U4.20 (SDA), U5.20 (SDA), U17.20 (SDA)
SEQ_BUTTON_1: R283.2, U17.12, U$59.2
SEQ_BUTTON_2: R284.2, U17.11, U$66.2
SS1: C18.1, R177.2, U16.9 (~SHDN/SS1)
SS2: C25.1, R179.2, U16.7 (~SHDN/SS2)
SS_OSC2: C58.2, U$51.P$1 (S1)
SS_OSC3: C60.2, U$57.P$1 (S1)
SW1: R245.2, U4.15, U$9.2
SW2: R246.2, U4.17, U$10.2
SW3: R259.2, U4.14, U$11.2
SW4: R260.2, U4.16, U$12.2
SW5: R261.2, U4.13, U$13.2
SW6: R262.2, U4.7 (P06), U$14.2
SW7: R263.2, U4.3 (P02), U$15.2
SW8: R264.2, U4.6 (P05), U$16.2
SW9: R265.2, U4.2 (P01), U$17.2
SW10: R266.2, U4.5 (P04), U$18.2
SW11: R267.2, U4.1 (P00), U$21.2
SW12: R268.2, U4.4 (P03), U$22.2
SW13: R269.2, U5.15, U$23.2
SW14: R270.2, U5.17, U$24.2
SW15: R271.2, U5.14, U$25.2
SW16: R272.2, U5.16, U$26.2
SW17: R273.2, U5.13, U$27.2
SW18: R274.2, U5.7 (P06), U$28.2
SW19: R275.2, U5.3 (P02), U$29.2
SW20: R276.2, U5.6 (P05), U$30.2
SW21: R277.2, U5.2 (P01), U$31.2
SW22: R278.2, U5.5 (P04), U$32.2
SW23: R279.2, U5.1 (P00), U$33.2
SW24: R280.2, U5.4 (P03), U$34.2
SYNC: U1.9 (!SYNC), U3.14 (PB2)
TIME_REVERSAL_2: C24.2, Q2.B (G), R59.2, U$1.18, U$36.7 (COL_OUT)
TIME_REVERSAL_3: C56.2, Q3.B (G), R67.2, U$2.18, U$38.7 (COL_OUT)
TRI_BUF_OSC1: R5.1, U$73.1 (OUT), U$73.2 (-IN)
TRI_OSC1: U$73.3 (+IN), U$105.1 (NO), U$108.1 (NO), VR2.2 (S)
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
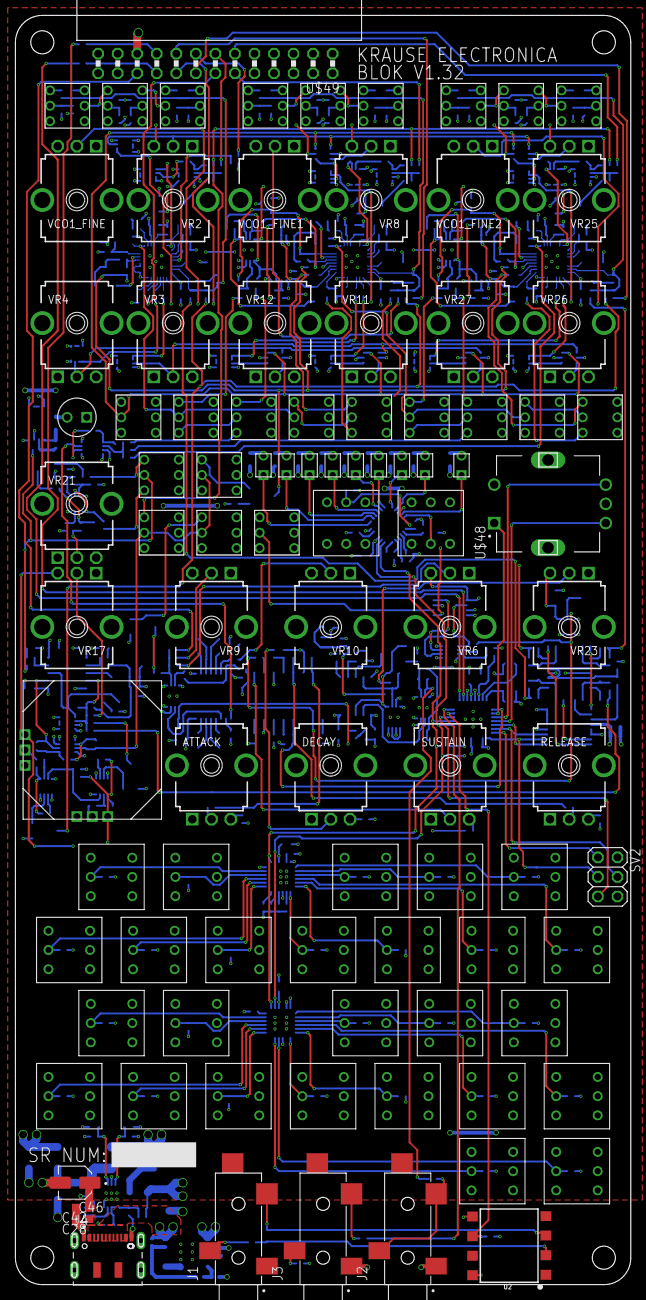
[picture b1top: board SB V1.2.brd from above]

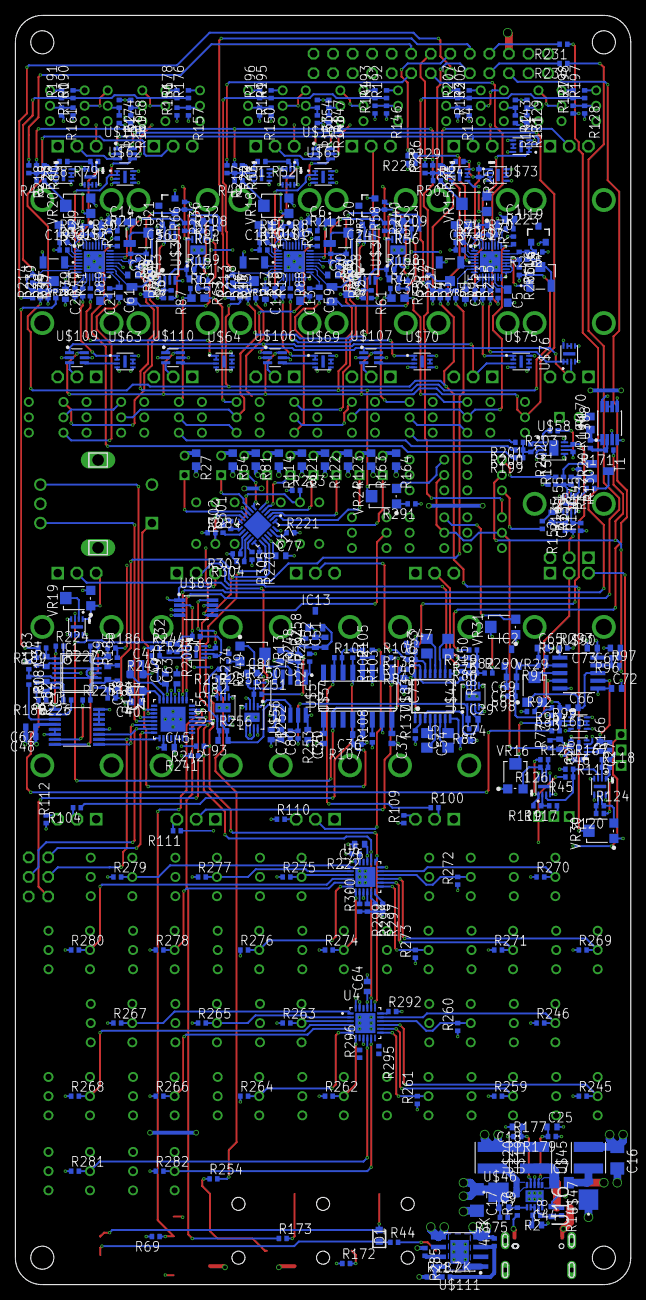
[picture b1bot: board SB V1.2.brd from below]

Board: 4 copper layers, 80.0 x 165.0 mm, 565 parts (470 on the bottom side), 426 nets.

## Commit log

2022-03-29 Updated Arduino
2024-10-23 stuff
